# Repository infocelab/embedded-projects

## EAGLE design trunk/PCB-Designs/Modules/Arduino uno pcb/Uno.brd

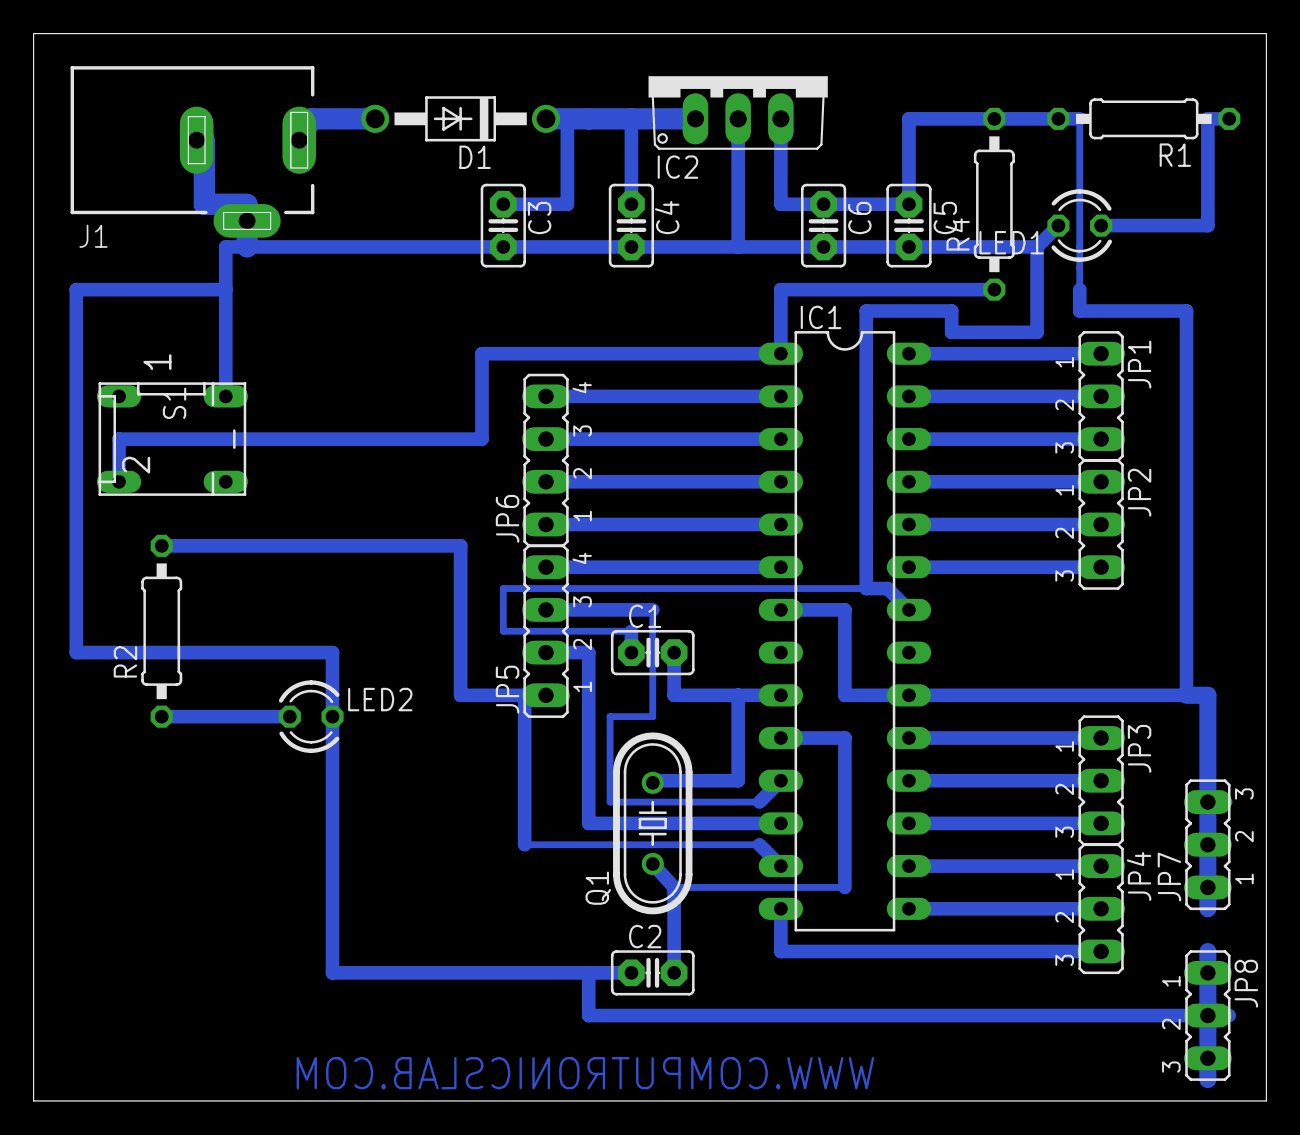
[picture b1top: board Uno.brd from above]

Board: 2 copper layers, 73.3 x 63.5 mm, 25 parts (0 on the bottom side), 29 nets.

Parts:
C1, C2: 22pf; C2.5-2
C3: 100UF; C2.5-2
C4, C5: 0.1uf; C2.5-2
C6: 4.7uf; C2.5-2
D1: 1N4007; DO41-10
IC1: ATMEGA328; DIL28-3
IC2: 7805; TO220V
J1: DCJ0303
JP1, JP2, JP3, JP4, JP7, JP8: JP2
JP5, JP6: JP4
LED1, LED2: LED3MM
Q1: 12MHZ; HC49/S
R1: 220R; 0207/10
R2: 330R; 0207/10
R4: 10K; 0207/10
S1: DP-02

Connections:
unnamed: C1.2, IC1.9, Q1.2
unnamed: C2.2, IC1.10, Q1.1
unnamed: D1.A, J1.1
unnamed: C5.1, C6.1, IC1.7, IC1.20, IC2.3, JP7.1, JP7.2, JP7.3, R1.2, R4.2
unnamed: C1.1, C2.1, C3.2, C4.2, C5.2, C6.2, IC1.22, IC2.2, J1.2, J1.3, JP8.1, JP8.2, JP8.3, LED1.K, LED2.K, S1.4
unnamed: LED1.A, R1.1
unnamed: C3.1, C4.1, D1.C, IC2.1
unnamed: IC1.28, JP1.1
unnamed: IC1.27, JP1.2
unnamed: IC1.26, JP1.3
unnamed: IC1.25, JP2.1
unnamed: IC1.24, JP2.2
unnamed: IC1.23, JP2.3
unnamed: IC1.5, JP6.1
unnamed: IC1.2, JP6.4
unnamed: IC1.3, JP6.3
unnamed: IC1.4, JP6.2
unnamed: IC1.6, JP5.4
unnamed: IC1.12, JP5.2
unnamed: IC1.11, JP5.3
unnamed: IC1.13, JP5.1, R2.2
unnamed: IC1.14, JP4.3
unnamed: IC1.15, JP4.2
unnamed: IC1.16, JP4.1
unnamed: IC1.17, JP3.3
unnamed: IC1.18, JP3.2
unnamed: IC1.19, JP3.1
unnamed: IC1.1, R4.1, S1.2
unnamed: LED2.A, R2.1

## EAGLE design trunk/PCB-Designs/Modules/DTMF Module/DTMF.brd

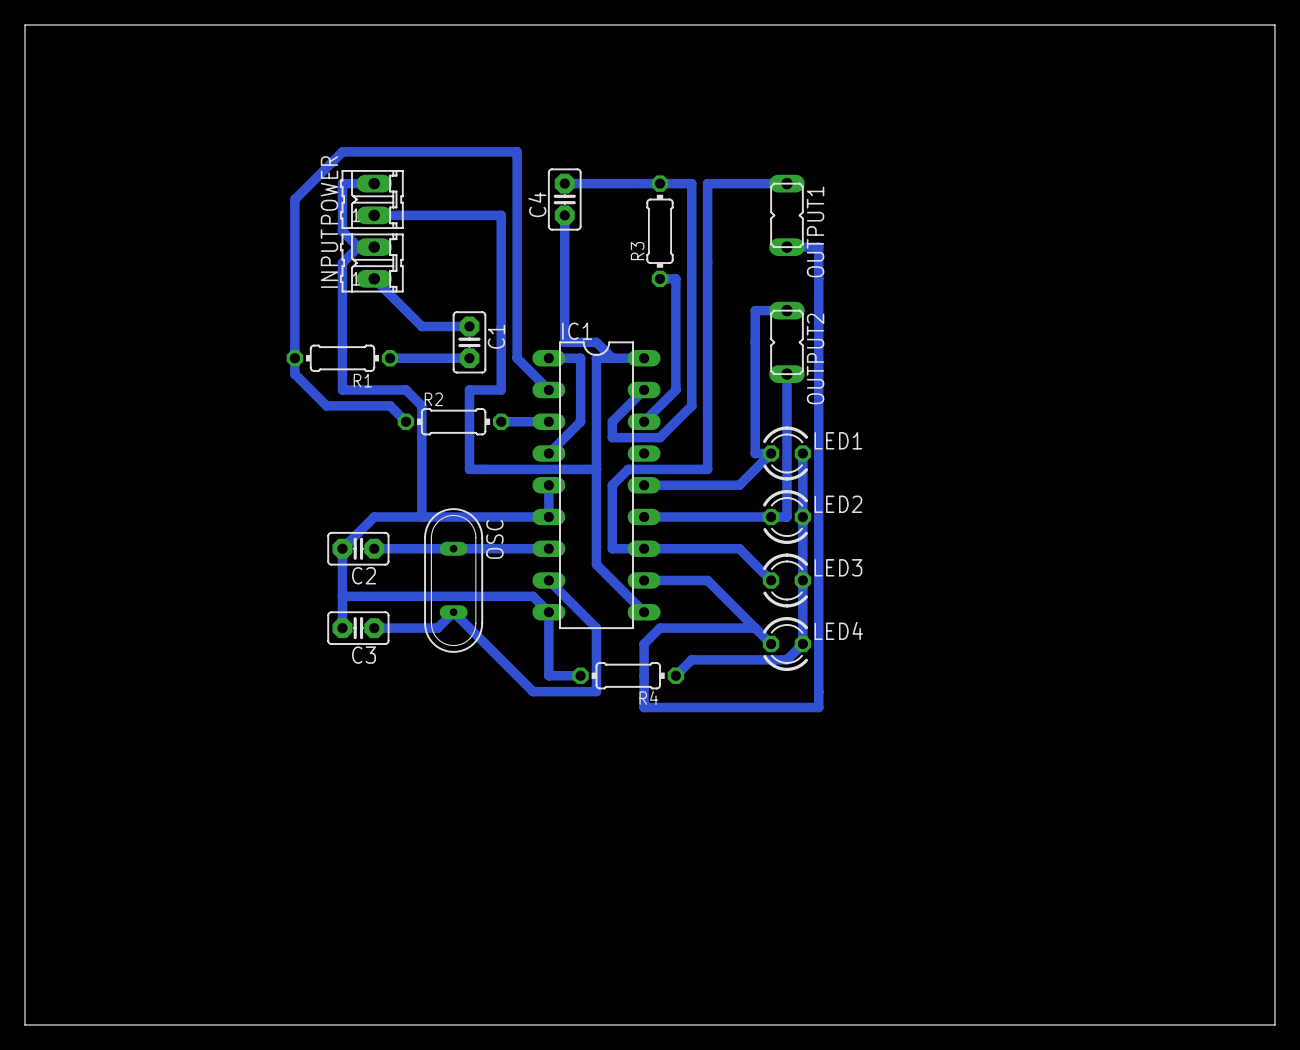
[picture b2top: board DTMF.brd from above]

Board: 2 copper layers, 100.0 x 80.0 mm, 18 parts (0 on the bottom side), 16 nets.

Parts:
C1: 0.47uf; C2.5-2
C2, C3: 22PF; C2.5-2
C4: 0.1UF; C2.5-2
IC1: CM8870CP; DIL18
INPUT: 02P
LED1, LED2, LED3, LED4: 3mm; LED3MM
OSC: 3.57; QS
OUTPUT1, OUTPUT2: JP1
POWER: 02P
R1: 10K; 0204/7
R2, R3: 100K; 0204/7
R4: 330E; 0204/7

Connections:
unnamed: C2.2, C3.2, IC1.5, IC1.6, IC1.9, INPUT.2, POWER.2, R4.2
unnamed: C1.2, R1.1
unnamed: IC1.3, R2.2
unnamed: LED1.K, LED2.K, LED3.K, LED4.K, R4.1
unnamed: IC1.11, LED4.A, OUTPUT1.2
unnamed: IC1.12, LED3.A, OUTPUT1.1
unnamed: IC1.13, LED2.A, OUTPUT2.2
unnamed: IC1.14, LED1.A, OUTPUT2.1
unnamed: C4.1, IC1.10, IC1.18, POWER.1
unnamed: C1.1, INPUT.1
unnamed: IC1.2, R1.2, R2.1
unnamed: IC1.1, IC1.4
unnamed: C2.1, IC1.7, OSC.1
unnamed: C3.1, IC1.8, OSC.2
unnamed: IC1.16, R3.1
unnamed: C4.2, IC1.17, R3.2

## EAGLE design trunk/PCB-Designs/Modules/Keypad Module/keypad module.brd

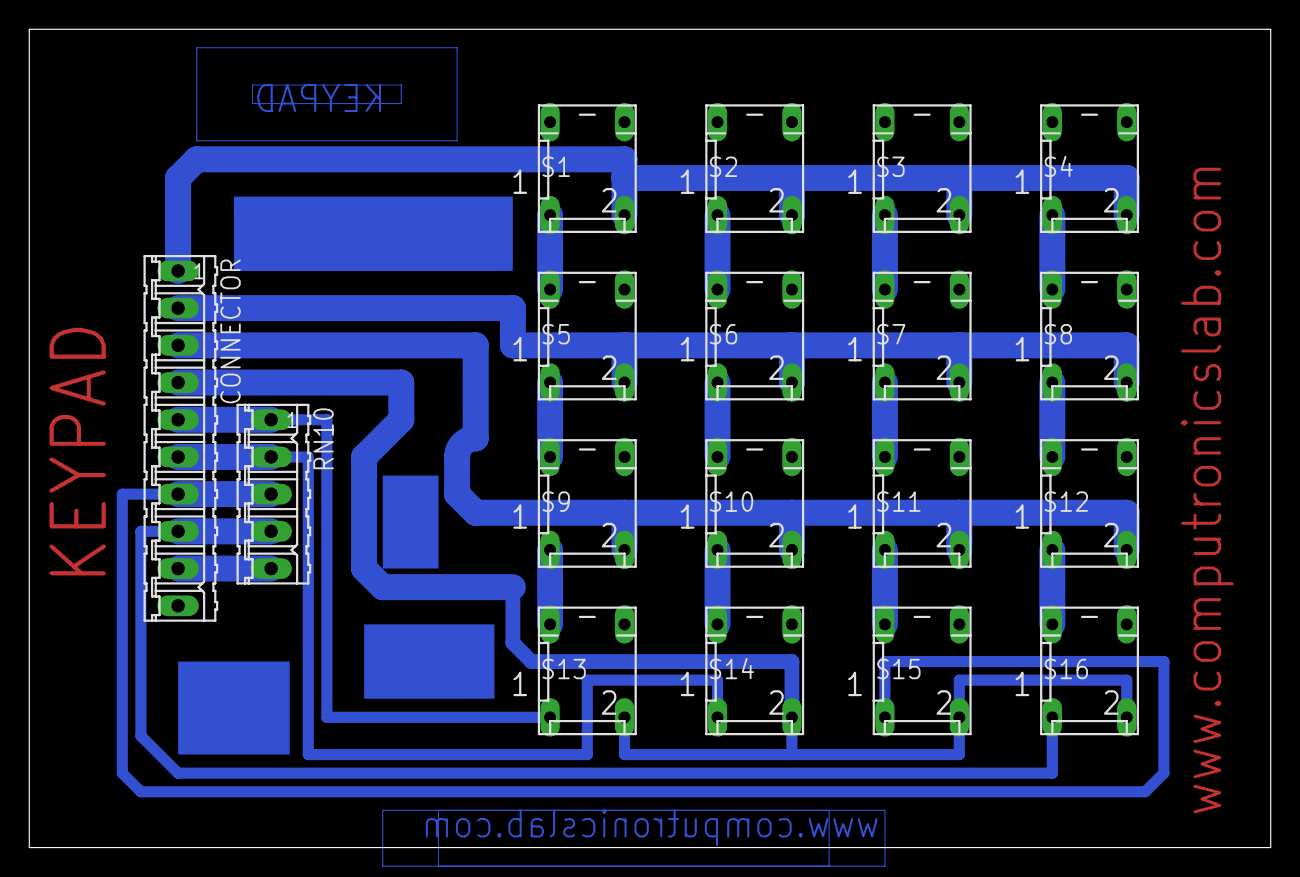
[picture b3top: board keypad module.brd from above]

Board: 2 copper layers, 84.8 x 55.9 mm, 18 parts (0 on the bottom side), 21 nets.

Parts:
CONNECTOR: 10pin; 10P
RN10: 5pin; 05P
S1, S2: push switch; DP-02
S3, S4, S5, S6, S7, S8, S9, S10, S11, S12, S13, S14, S15, S16: DP-02

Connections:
unnamed: CONNECTOR.1, S1.2, S2.2, S3.2, S4.2
unnamed: CONNECTOR.2, S5.2, S6.2, S7.2, S8.2
unnamed: CONNECTOR.3, S9.2, S10.2, S11.2, S12.2
unnamed: S7.1, S11.4
unnamed: S1.1, S5.4
unnamed: S5.1, S9.4
unnamed: S9.1, S13.4
unnamed: S2.1, S6.4
unnamed: S6.1, S10.4
unnamed: S10.1, S14.4
unnamed: S3.1, S7.4
unnamed: S4.1, S8.4
unnamed: S11.1, S15.4
unnamed: S12.1, S16.4
unnamed: S8.1, S12.4
unnamed: CONNECTOR.4, S13.2, S14.2, S15.2, S16.2
unnamed: CONNECTOR.5, RN10.1, S13.1
unnamed: CONNECTOR.6, RN10.2, S14.1
unnamed: CONNECTOR.7, RN10.3, S15.1
unnamed: CONNECTOR.8, RN10.4, S16.1
unnamed: CONNECTOR.9, RN10.5

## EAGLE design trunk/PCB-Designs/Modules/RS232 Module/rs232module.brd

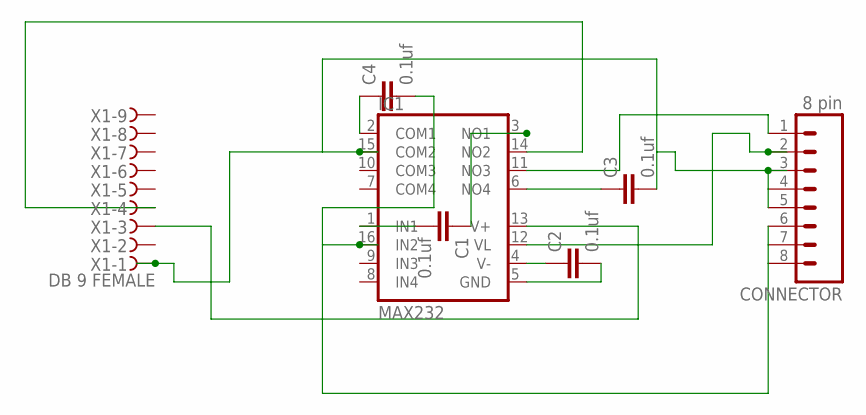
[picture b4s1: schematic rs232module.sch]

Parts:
C1, C2, C3, C4: 0.1uf; C2.5-3
CONNECTOR: 8 pin; 08P
IC1: MAX232; DIL16
X1: DB 9 FEMALE; H2M09ST

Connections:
unnamed: C1.2, IC1.1 (IN1)
unnamed: C1.1, IC1.3 (NO1)
unnamed: C2.1, IC1.4 (V-)
unnamed: C2.2, IC1.5 (GND)
unnamed: C3.1, IC1.6 (NO4)
unnamed: C3.2, CONNECTOR.3, CONNECTOR.4, CONNECTOR.5, IC1.15 (COM2), X1.1
unnamed: C4.1, IC1.2 (COM1)
unnamed: C4.2, CONNECTOR.6, CONNECTOR.7, CONNECTOR.8, IC1.16 (IN2)
unnamed: IC1.13 (V+), X1.3
unnamed: IC1.14 (NO2), X1.4
unnamed: CONNECTOR.1, IC1.11 (NO3)
unnamed: CONNECTOR.2, IC1.12 (VL)

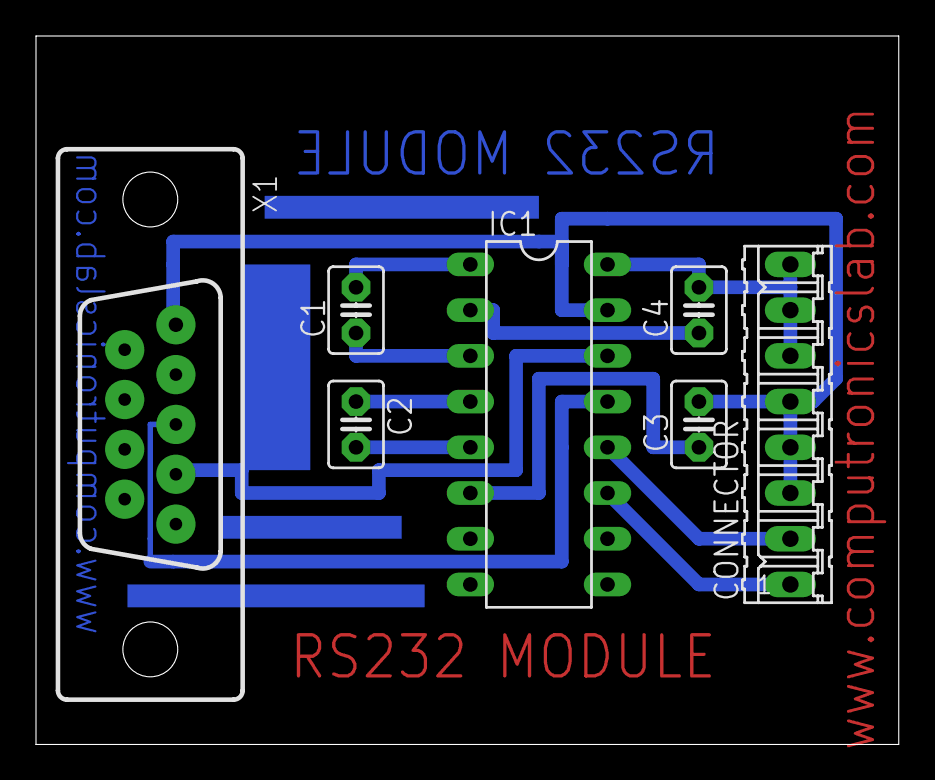
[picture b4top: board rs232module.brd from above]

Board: 2 copper layers, 47.9 x 39.4 mm, 7 parts (0 on the bottom side), 12 nets.

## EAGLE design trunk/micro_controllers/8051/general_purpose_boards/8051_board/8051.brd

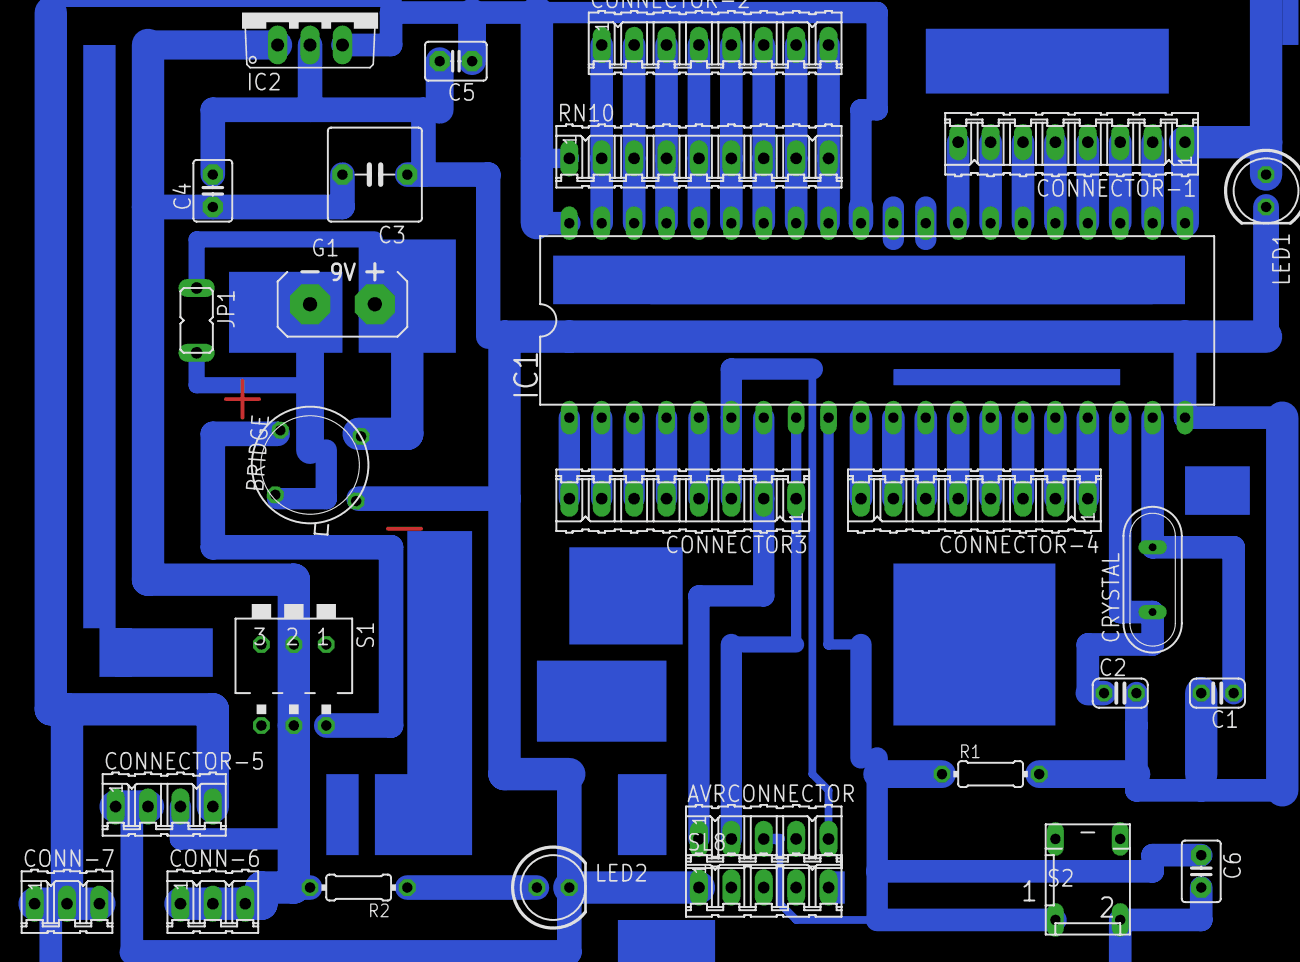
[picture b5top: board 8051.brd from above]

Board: 2 copper layers, 28 parts (0 on the bottom side), 42 nets.

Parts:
AVRCONNECTOR: 05P
BRIDGE: TO39/4
C1, C2: 33pf; C025-024X044
C3: 470uf; C5B7.2
C4: .01uf; C2.5-3
C5: 4.7uf; C2.5-3
C6: 0.1uf; C2.5-3
CONN-6, CONN-7: 3 pin; 03P
CONNECTOR3: 8 pin; 08P
CONNECTOR-1, CONNECTOR-2, CONNECTOR-4: 8 pin; 08P
CONNECTOR-5: 4 pin; 04P
CRYSTAL: 11.0592 mhz; QS
G1: AB9V
IC1: AT89S51; DIL40
IC2: 7805TV; TO220V
JP1: TRANSFORMER; JP1
LED1, LED2: 5mm; LED5MM
R1: 10k; 0204/7
R2: 560E; 0204/7
RN10: 10 k; 09P
S1: DA-03
S2: push switch; DP-02
SL8: 05P

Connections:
unnamed: C2.1, CRYSTAL.1, IC1.18
unnamed: C1.1, CRYSTAL.2, IC1.19
unnamed: C3.2, C4.1, CONN-6.1, CONN-6.2, CONN-6.3, CONNECTOR-5.3, IC2.1, R2.2, S1.5
unnamed: BRIDGE.2, G1.+, JP1.1
unnamed: CONNECTOR-4.8, IC1.10
unnamed: CONNECTOR-4.7, IC1.11
unnamed: CONNECTOR-4.6, IC1.12
unnamed: CONNECTOR-4.5, IC1.13
unnamed: CONNECTOR-4.4, IC1.14
unnamed: CONNECTOR-4.3, IC1.15
unnamed: CONNECTOR-4.2, IC1.16
unnamed: CONNECTOR-4.1, IC1.17
unnamed: AVRCONNECTOR.3, C6.1, IC1.9, R1.1, S2.1
unnamed: AVRCONNECTOR.1, CONNECTOR3.2, IC1.7
unnamed: BRIDGE.4, G1.-, JP1.2
unnamed: CONNECTOR3.4, IC1.5
unnamed: CONNECTOR3.5, IC1.4
unnamed: CONNECTOR3.6, IC1.3
unnamed: CONNECTOR3.7, IC1.2
unnamed: CONNECTOR3.8, IC1.1
unnamed: CONNECTOR-2.1, IC1.39, RN10.2
unnamed: CONNECTOR-2.2, IC1.38, RN10.3
unnamed: CONNECTOR-2.3, IC1.37, RN10.4
unnamed: CONNECTOR-2.4, IC1.36, RN10.5
unnamed: CONNECTOR-2.5, IC1.35, RN10.6
unnamed: CONNECTOR-2.6, IC1.34, RN10.7
unnamed: CONNECTOR-2.7, IC1.33, RN10.8
unnamed: CONNECTOR-2.8, IC1.32, RN10.9
unnamed: CONNECTOR-1.1, IC1.21, LED1.A
unnamed: CONNECTOR-1.2, IC1.22
unnamed: CONNECTOR-1.3, IC1.23
unnamed: CONNECTOR-1.4, IC1.24
unnamed: CONNECTOR-1.5, IC1.25
unnamed: CONNECTOR-1.6, IC1.26
unnamed: CONNECTOR-1.7, IC1.27
unnamed: CONNECTOR-1.8, IC1.28
unnamed: C5.1, C6.2, CONN-7.1, CONN-7.2, CONN-7.3, CONNECTOR-5.4, IC1.31, IC1.40, IC2.3, RN10.1, S2.2
unnamed: BRIDGE.1, C1.2, C2.2, C3.1, C4.2, C5.2, CONNECTOR-5.1, CONNECTOR-5.2, IC1.20, IC2.2, LED1.K, LED2.K, R1.2, SL8.1
unnamed: AVRCONNECTOR.5, CONNECTOR3.3, IC1.6
unnamed: LED2.A, R2.1
unnamed: AVRCONNECTOR.2, CONNECTOR3.1, IC1.8
unnamed: BRIDGE.3, S1.6

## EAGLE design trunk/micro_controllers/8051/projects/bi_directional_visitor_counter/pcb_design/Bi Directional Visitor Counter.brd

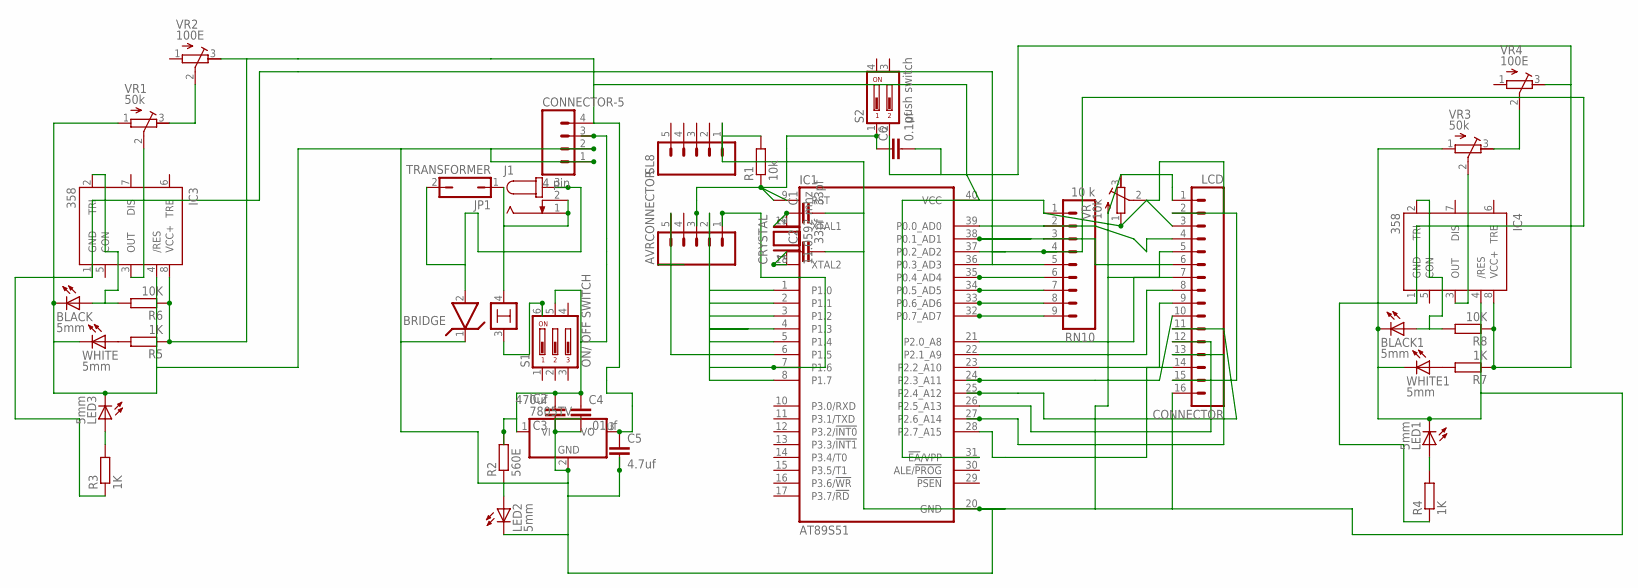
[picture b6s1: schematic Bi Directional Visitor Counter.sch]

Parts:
AVRCONNECTOR: M05; 05P
BLACK, BLACK1: 5mm; LED5MM
BRIDGE: LM399H; TO39/4
C1, C2: 33pf; C025-024X044
C3: 470uf; C5B7.2
C4: .01uf; C2.5-3
C5: 4.7uf; C2.5-3
C6: 0.1uf; C2.5-6
CONNECTOR: LCD; 16P
CONNECTOR-5: 4 pin; 04P
CRYSTAL: 11.0592 mhz; QS
IC1: AT89S51; DIL40
IC2: 7805TV; TO220V
IC3, IC4: 358; DIL-08
J1: JACK-PLUG0; SPC4077
JP1: TRANSFORMER; JP1
LED1, LED2, LED3: 5mm; LED5MM
R1: 10k; 0204/7
R2: 560E; 0204/7
R3, R4, R5, R7: 1K; 0204/7
R6, R8: 10K; 0204/7
RN10: 10 k; 09P
S1: ON/ OFF SWITCH; DA-03
S2: push switch; DP-02
SL8: M05; 05P
VR: 10k; RTRIM64P
VR1, VR3: 50k; RTRIM64P
VR2, VR4: 100E; RTRIM64P
WHITE, WHITE1: 5mm; LED5MM

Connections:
unnamed: C2.1, CRYSTAL.1, IC1.18 (XTAL2)
unnamed: C1.1, CRYSTAL.2, IC1.19 (XTAL1)
unnamed: BRIDGE.2, J1.3, JP1.2
unnamed: C3.2, C4.1, CONNECTOR-5.3, IC2.1 (VI), R2.2, S1.5
unnamed: C5.1, C6.2, CONNECTOR.2, CONNECTOR.15, CONNECTOR-5.4, IC1.31 (!EA!/VPP), IC1.40 (VCC), IC2.3 (VO), IC3.8 (VCC+), IC4.8 (VCC+), R5.1, R6.1, R7.1, R8.1, RN10.1, S2.2, VR.1 (E), VR2.3 (A), VR4.3 (A)
unnamed: IC1.36 (P0.3_AD3), IC3.1 (GND), R3.1, RN10.5
unnamed: R5.2, WHITE.A
unnamed: BLACK.A, IC3.2 (TRI), R6.2
unnamed: IC3.3 (OUT), VR1.2 (S)
unnamed: VR1.3 (A), VR2.2 (S)
unnamed: AVRCONNECTOR.3, C6.1, IC1.9 (RST), R1.1, S2.1
unnamed: AVRCONNECTOR.1, IC1.7 (P1.6)
unnamed: BRIDGE.4, J1.1, J1.2, JP1.1
unnamed: LED3.A, R3.2
unnamed: IC1.35 (P0.4_AD4), RN10.6
unnamed: IC1.34 (P0.5_AD5), RN10.7
unnamed: IC1.33 (P0.6_AD6), RN10.8
unnamed: IC1.32 (P0.7_AD7), RN10.9
unnamed: CONNECTOR.7, IC1.21 (P2.0_A8)
unnamed: CONNECTOR.8, IC1.22 (P2.1_A9)
unnamed: CONNECTOR.9, IC1.23 (P2.2_A10)
unnamed: IC1.37 (P0.2_AD2), IC4.1 (GND), R4.1, RN10.4
unnamed: CONNECTOR.12, IC1.26 (P2.5_A13)
unnamed: R7.2, WHITE1.A
unnamed: BLACK1.A, IC4.2 (TRI), R8.2
unnamed: CONNECTOR.3, VR.2 (S)
unnamed: IC4.3 (OUT), VR3.2 (S)
unnamed: BLACK.K (C), BLACK1.K (C), BRIDGE.1, C1.2, C2.2, C3.1, C4.2, C5.2, CONNECTOR.1, CONNECTOR.5, CONNECTOR.16, CONNECTOR-5.1, CONNECTOR-5.2, IC1.20 (GND), IC2.2 (GND), IC3.4 (/RES), IC4.4 (/RES), LED1.K (C), LED2.K (C), LED3.K (C), R1.2, SL8.1, VR.3 (A), VR1.1 (E), VR3.1 (E), WHITE.K (C), WHITE1.K (C)
unnamed: AVRCONNECTOR.5, IC1.6 (P1.5)
unnamed: LED2.A, R2.1
unnamed: VR3.3 (A), VR4.2 (S)
unnamed: AVRCONNECTOR.2, IC1.8 (P1.7)
unnamed: BRIDGE.3, S1.6
unnamed: CONNECTOR.6, IC1.38 (P0.1_AD1), RN10.3
unnamed: LED1.A, R4.2
unnamed: CONNECTOR.10, IC1.24 (P2.3_A11)
unnamed: CONNECTOR.11, IC1.25 (P2.4_A12)
unnamed: CONNECTOR.13, IC1.27 (P2.6_A14)
unnamed: CONNECTOR.14, IC1.28 (P2.7_A15)
unnamed: CONNECTOR.4, IC1.39 (P0.0_AD0), RN10.2

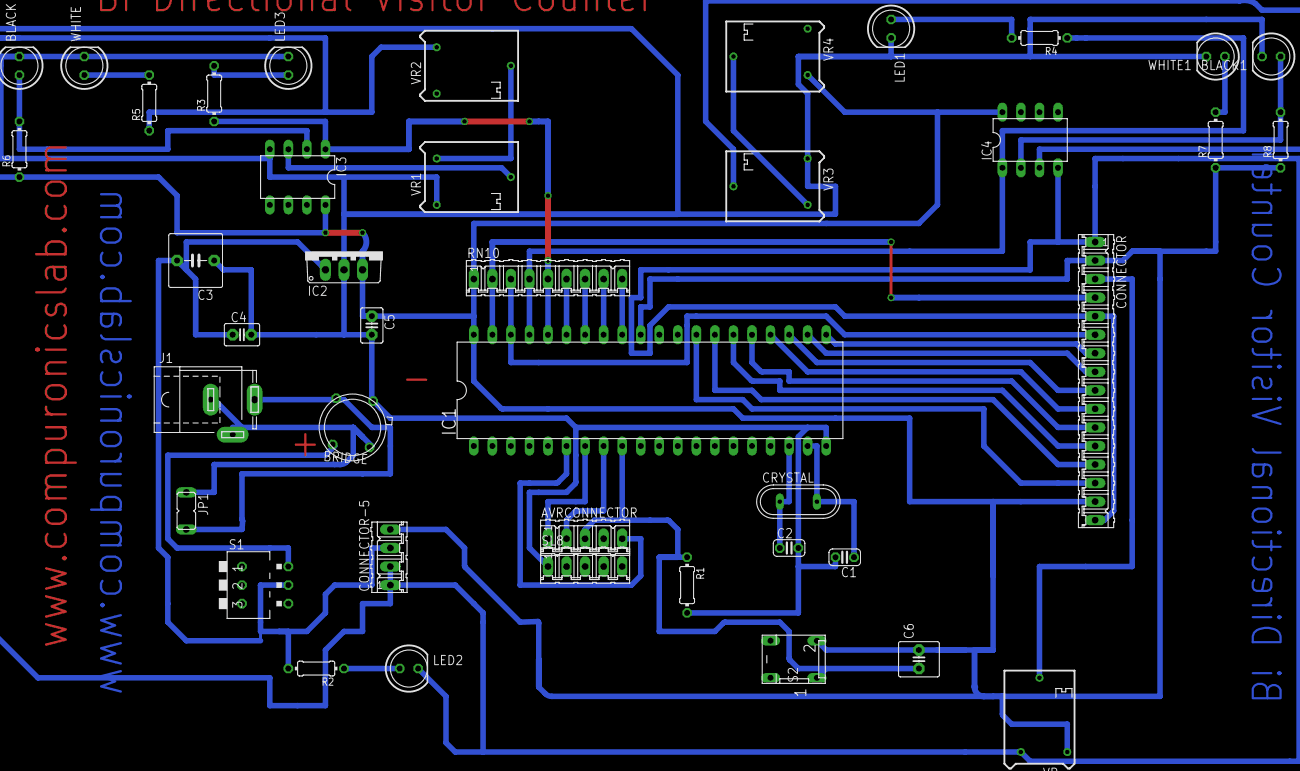
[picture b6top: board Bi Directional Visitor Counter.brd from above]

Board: 2 copper layers, 41 parts (0 on the bottom side), 40 nets.
